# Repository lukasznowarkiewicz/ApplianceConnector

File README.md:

# Appliance connector

## Initial idea - visible gap on the market

The history behing this device came from my experience - I used to install smart home systems and saw some market gap in integrating smart home devices which oryginally was not intended to be "smart". I have in mind devices controlled over infrared, like air condationers, TVs, home theaters, audio systems, satellite and cable boxes, projectors, controlled over serial port (RS-232), like projectors, some audio entertainment systems, video conferencing systems, surveillance camera systems, etc., finishing on most simple, controlled with dry contact, like garage and gate openers, access control systems or blinds and curtains systesm, to just name a few. Backbone of most smart home systems in the end, almost always is TCP/IP network. Proabably the most universal method between both vendor locked and open smart home systems is communication via REST API. This device main prupose was to cover this gap, allow integration of all listed devices in thoughtfully manner. 

## Similar devices

Back in 2019, when we were working on this device, already some alternatives existed. There were deivces, which adresses only part of the problem. To list a few:

### Global Cache iTach

- **Pros**: Supports various connection options, compact, compatible with many systems.
- **Cons**: Setup complexity, may not suit simple needs, separate devices for RS232 and IR, high price

### BroadLink RM Pro+

- **Pros**: Affordable, supports IR and RF 433MHz, works with major voice assistants.
- **Cons**: RF control issues reported, app usability, lack of REST API.

### Remotec AC Master ZXT-600

- **Pros**: Specialized for AC control, supports major brands, energy-efficient.
- **Cons**: Limited to AC, setup complexity with certain hubs, lack of REST API.

### Blastbot IR Blaster

- **Pros**: Smartphone and voice control, supports schedules.
- **Cons**: Cloud dependency, IR only, lack of REST API.

### Remotec ZXT-310US

- **Pros**: Z-Wave to IR for AV devices, supports learning IR codes.
- **Cons**: Focus on AV, manual configuration for uncommon devices, lack of REST API.

### Hank IR Transceiver

- **Pros**: Z-Wave Plus, IR learning, compact.
- **Cons**: AV control focus, setup technicality, lack of REST API.

### Xiaomi Universal IR Remote Controller

- **Pros**: Very affordable, wide device support, integrates with Mi Home.
- **Cons**: Wi-Fi dependency, app/setup challenges for non-Chinese speakers, lack of REST API.

### Logitech Harmony

- **Pros**: Broad device compatibility, advanced automation, supports multiple connection types.
- **Cons**: Higher cost, discontinued models may affect support, lack of REST API.

## First prototype

First prototype was rough. Designed in `Autodesk Eagle` (shortly after buying it from CadSoft). It only purpose was to get rid off breadboards, which often cause more problems than circuit itself. This devkit was an extension to `Lolin32 Lite` prototyping board. This board I would call as "it ain't much, but it honest work" and most important allowed us quick start working on the software.

It has necessary components for testing initially agreed functionalities:
- IR leds for controlling devices
- IR receiver `PNA460XM`
- two experimental touch buttons (ESP32 has itself option for capacitive buttons support, but in the end we were unable to figure out how to make it work)
- connector for `TTTP223` based touch button module
- `WS2812B` Leds for showing status of the device

## Functional requirements and UI design

At this point we more or less know how device should function, which features implement. Form of the device was not clear yet, but anyway it didn't stop us from working on software. Basic user interface was designed in `Affinity Designer`. Simple mockup of the software, not functional, but give us good base for creating user interface in web technologies.

## Software Development

The web server runs directly on the ESP32, necessitating that the webpage be as simple and lightweight as possible. With only 4MB of storage available, every kilobyte counted. Most images used were .svg, and wherever feasible, they were generated using CSS to save space.

The ESP32 operates on `ESP-IDF FreeRTOS`. Developing such an advanced application in plain C—especially incorporating functions like Wi-Fi connection, filesystem management, and web server functionalities—would significantly increase the app's complexity.

### Frontend

Given the storage limitations, the frontend was designed to be straightforward and lightweight. This is why we opted not to use any frameworks for creating the GUI. It was crafted using simple HTML, with CSS for styling and JavaScript for websockets to minimize overhead and ensure efficiency.

https://github.com/lukasznowarkiewicz/ApplianceConnector/assets/82212257/3271daf3-c359-4126-b65f-c0a6bbfbe71e

### Backend

The backend of this application on the ESP32, utilizing ESP-IDF FreeRTOS, comprises various components, each managed by specific files:

- **Webserver**: `webserver.c` and `webserver.h` handle HTTP requests, serving the GUI files and processing API calls from the frontend. `webserver_types.h` likely defines the structures and enums used by the webserver.

- **Wi-Fi Connection**: `netConf.c` and `netConf.h` are responsible for configuring the Wi-Fi connection, handling tasks such as connecting to the Wi-Fi network and managing network settings.

- **Infrared Control**:
  - Sending IR commands: `irsend.c` and `irsend.h` manage the sending of IR commands to devices.
  - Receiving IR commands: `irrecv.c` and `irrecv.h` handle the reception of IR signals from remote controls.

- **UART Communication**: `tcpserial.c` and `tcpserial.h` handle of UART communication.

- **LED Control**: `led.c` and `led.h` are used for controlling LED indicators on the ESP32, such as showing the status of the device or Wi-Fi connection.

- **Relay Control**: `relay.c` and `relay.h` manage the activation and deactivation of relays for controlling dry contacts.

- **Button Input**: `button.c` and `button.h` handle input from physical buttons on the ESP32 device, allowing for user interaction without the web interface.

### Testing infrared

Testing receiving commands from IR:

https://github.com/lukasznowarkiewicz/ApplianceConnector/assets/82212257/00d33be0-9f63-4c23-b90f-50ff3d0fc727

Testing sending commands over IR:

https://github.com/lukasznowarkiewicz/ApplianceConnector/assets/82212257/5f554944-b339-42f7-858e-584611f51841

Saving received commands to text file (as a config):

https://github.com/lukasznowarkiewicz/ApplianceConnector/assets/82212257/204f5668-1959-4dcd-b433-fa26de5b123a

### Testing UART

https://github.com/lukasznowarkiewicz/ApplianceConnector/assets/82212257/dbb3c007-76f6-457e-a3c8-33a27682dad4

### Testing relays

https://github.com/lukasznowarkiewicz/ApplianceConnector/assets/82212257/7d674879-574c-41a6-804a-36f65532bcf2

## Enclosure

After we made first functioning prorotype - it was time to pack this device into sleek housing. Many ideas was both designed and 3d printed. 

Casing was designed in Fusion360:

REV 5 is the last casing we stick to and designed custom board for it. It has touch button on the top, translucent casing allowing both IR and visible light from RGB LEDs to go through, place at the bottom for slide-in mounting brackets (allowing for mounting it on the ceiling, to ziptie to something, etc.)

## Hardware

Electronic part of the design consists mainly on two boards:
- upper one with ESP32 module, IR LEDs and IR receiver
- lower one with terminal blocks for screwing wires of the RS232 device, dry contact controlled deivces, supply power via terminal block, side or bottom micro-USB cable and headphone jacks for connecting remote IR transmitters. Hole in the middle allow guiding wires through and then wrap them around the deivce.

In the folder `hardwareElectronics` `Eagle` project can be found. Unfortunately the most recent version has been lost and I've simply attached the last backup I could find.

## Project abandon

Due to start of the studies and lack of free time, this project died spontaneously. Now when I'm pushing those assets and writing this readme (about the time of finishing my masters degree) I look at it with a wink. Today with ease I've found a few of the market devices doing exactly that. Even cool project ESPHome does exactly that. But overall at the time it was great experiece.

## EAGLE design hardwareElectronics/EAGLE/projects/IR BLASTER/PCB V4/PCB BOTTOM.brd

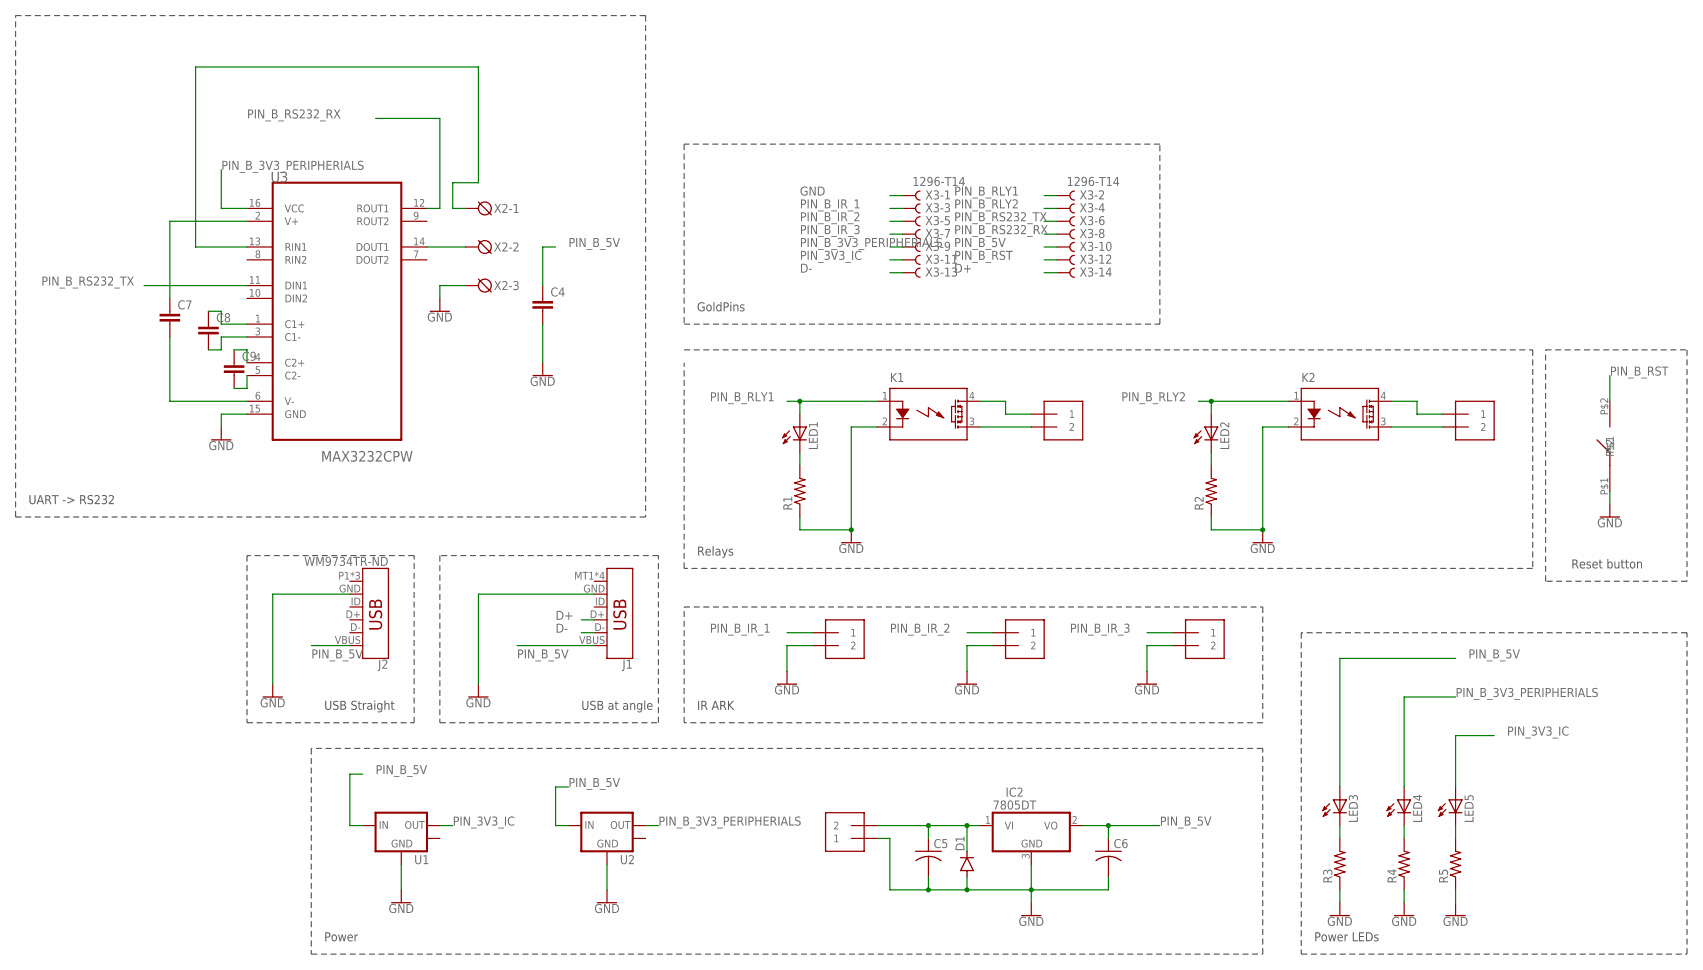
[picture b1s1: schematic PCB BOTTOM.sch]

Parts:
C4, C7, C8, C9: C-EUC0805K; C0805K
C5, C6: C-USC1206K; C1206K
D1: DIODE-SOD80C; SOD80C
IC2: 7805DT; TO252
IR1, IR2, IR3: 1X2-3.5MM
J1: USB_MICRO-B_SMT; USB-MICROB
J2: WM9734TR-ND; USB-B-MICRO-SMD_VERT
K1, K2: CPC1008N; SOIC-4-2.54
LED1, LED2, LED3, LED4, LED5: LEDCHIP-LED0805; CHIP-LED0805
PWR: 1X2-3.5MM
R1, R2, R3, R4, R5: R-US_M0805; M0805
RLY1, RLY2: 1X2-3.5MM
U1, U2: LM1117-1.8; SOT223
U3: MAX3232CPW; SOP65P640X120-16N
U$1: MICRO_SWITCH_AT_ANGLE
X2: DG3XX-03-3.5; DG350-3.5-03P
X3: 1296-T14; 1296-14

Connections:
D+: J1.D+, X3.14
D-: J1.D-, X3.13
GND: C4.2, C5.2, C6.2, D1.A, IC2.3 (GND), IR1.2, IR2.2, IR3.2, J1.GND, J2.GND, K1.2 (K), K2.2 (K), PWR.1, R1.1, R2.1, R3.1, R4.1, R5.1, U1.1 (GND), U2.1 (GND), U3.15 (GND), U$1.P$1, X2.3, X3.1
unnamed: K1.3 (D2), RLY1.2
unnamed: K1.4 (D1), RLY1.1
unnamed: LED1.C, R1.2
unnamed: K2.3 (D2), RLY2.2
unnamed: K2.4 (D1), RLY2.1
unnamed: LED2.C, R2.2
unnamed: U3.14 (DOUT1), X2.2
unnamed: U3.13 (RIN1), X2.1
unnamed: LED3.C, R3.2
unnamed: LED4.C, R4.2
unnamed: LED5.C, R5.2
unnamed: C7.1, U3.2 (V+)
unnamed: C7.2, U3.6 (V-)
unnamed: C9.1, U3.4 (C2+)
unnamed: C9.2, U3.5 (C2-)
unnamed: C8.2, U3.3 (C1-)
unnamed: C5.1, D1.C, IC2.1 (VI), PWR.2
unnamed: C8.1, U3.1 (C1+)
PIN_3V3_IC: LED5.A, U1.2 (OUT), X3.11
PIN_B_3V3_PERIPHERIALS: LED4.A, U2.2 (OUT), U3.16 (VCC), X3.9
PIN_B_5V: C4.1, C6.1, IC2.2 (VO), J1.VBUS, J2.VBUS, LED3.A, U1.3 (IN), U2.3 (IN), X3.10
PIN_B_IR_1: IR1.1, X3.3
PIN_B_IR_2: IR2.1, X3.5
PIN_B_IR_3: IR3.1, X3.7
PIN_B_RLY1: K1.1 (A), LED1.A, X3.2
PIN_B_RLY2: K2.1 (A), LED2.A, X3.4
PIN_B_RS232_RX: U3.12 (ROUT1), X3.8
PIN_B_RS232_TX: U3.11 (DIN1), X3.6
PIN_B_RST: U$1.P$2, X3.12

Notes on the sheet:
USB Straight
USB at angle
Power
IR ARK
Power LEDs
Reset button
Relays
GoldPins
UART -> RS232

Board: 2 copper layers, 34 parts (3 on the bottom side), 32 nets, no tracks yet.

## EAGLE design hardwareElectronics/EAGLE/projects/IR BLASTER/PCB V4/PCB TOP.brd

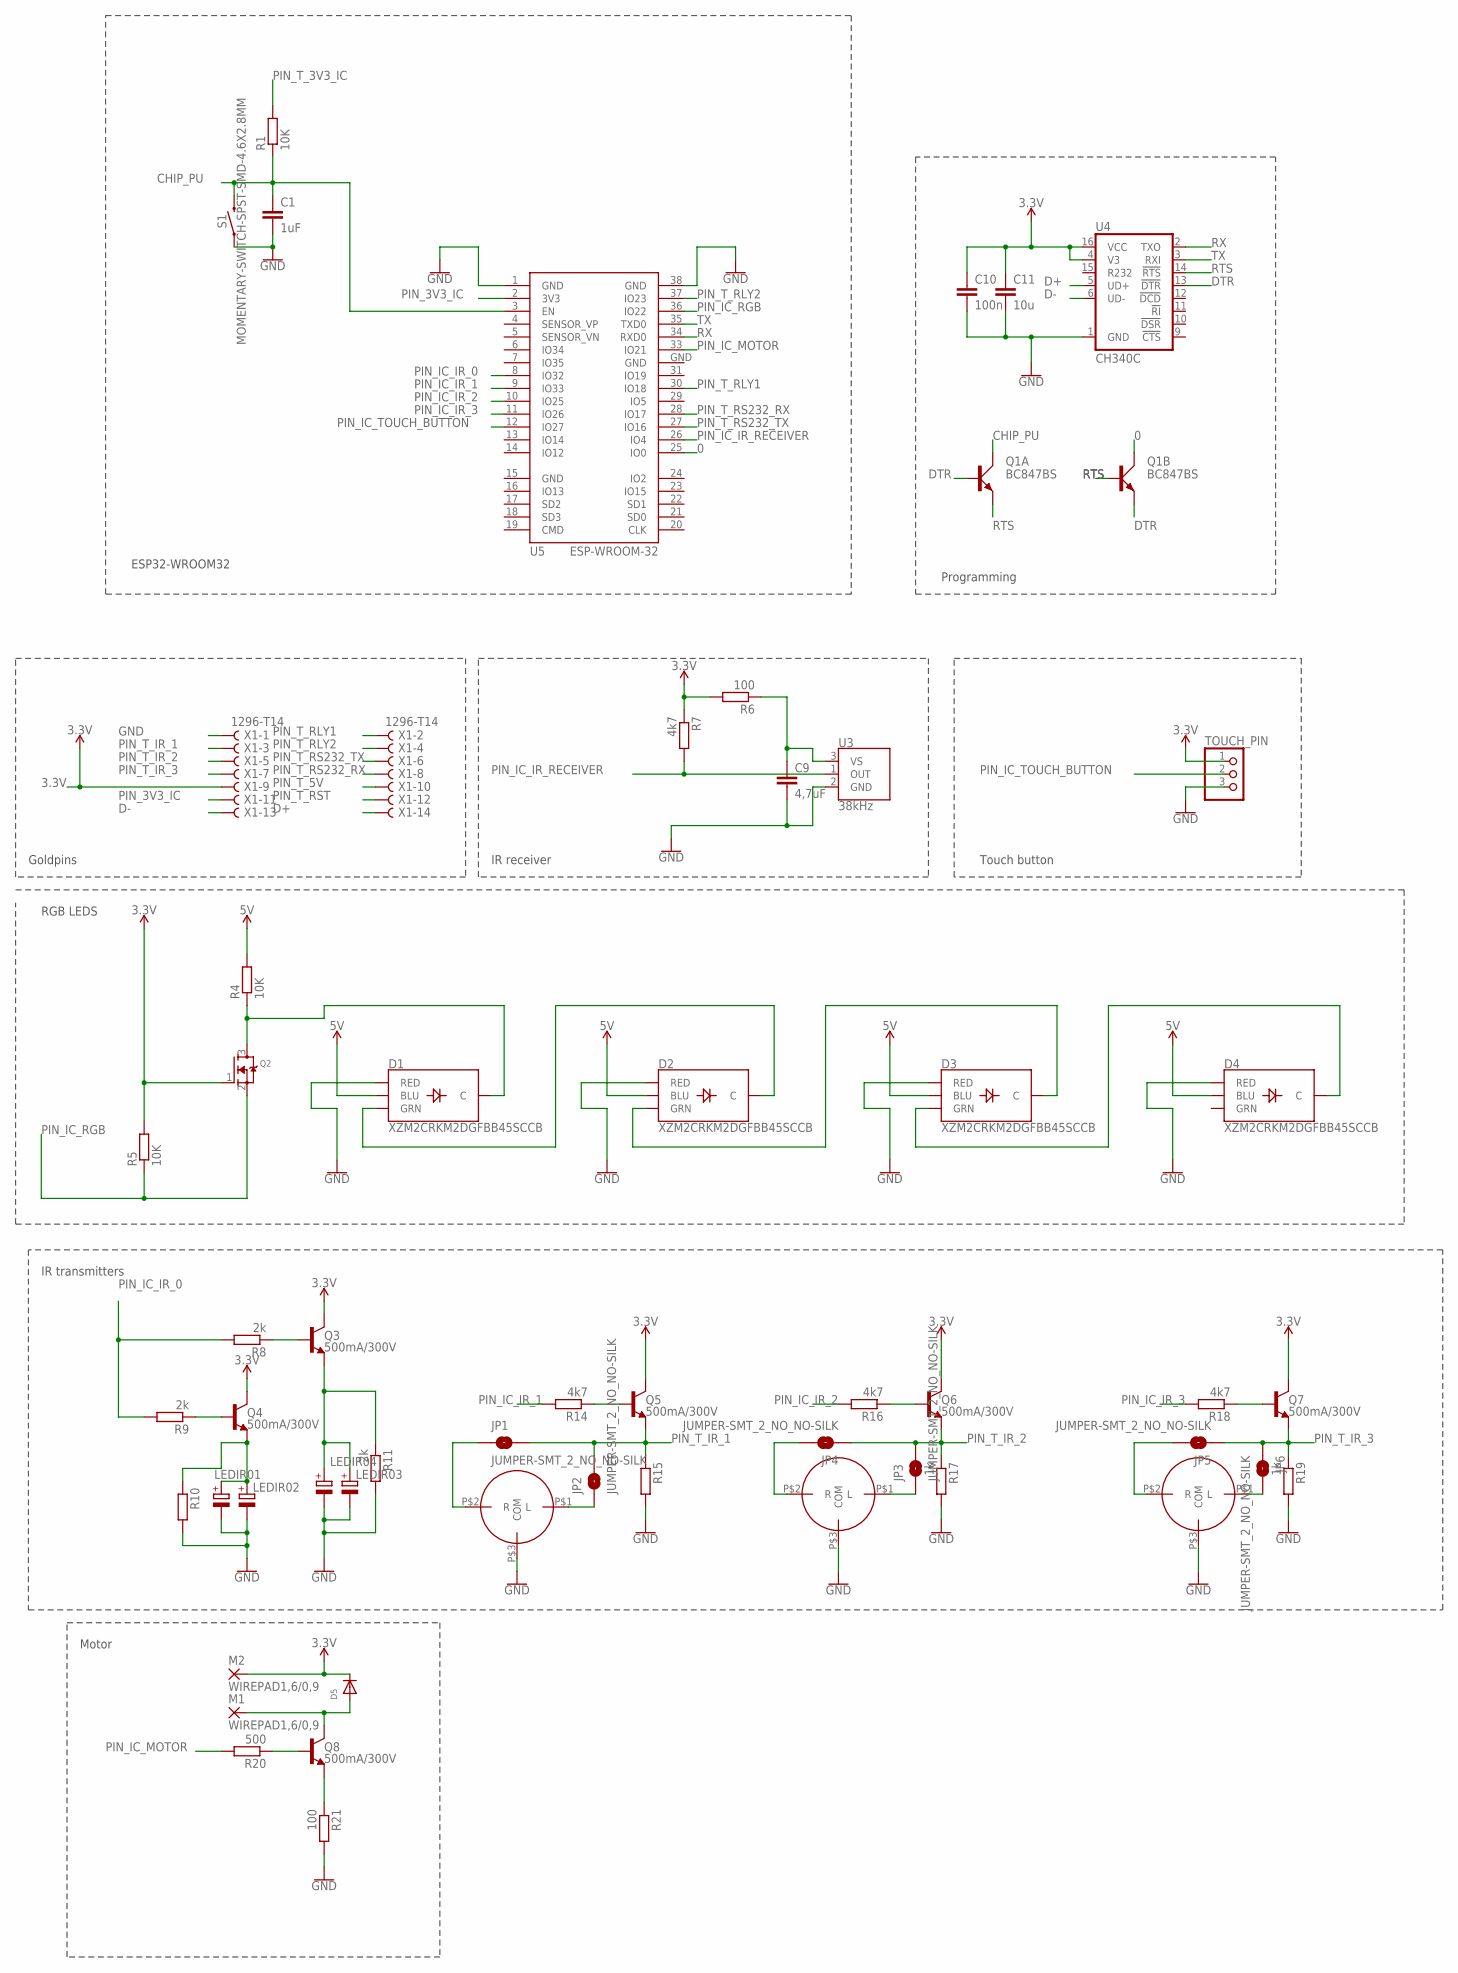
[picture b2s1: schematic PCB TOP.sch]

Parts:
C1: 1uF; C0603K
C9: 4,7uF; C0603K
C10: 100n; C0603K
C11: 10u; C0603K
D1, D2, D3, D4: XZM2CRKM2DGFBB45SCCB; PLCC4SMDLED
D5: DIODESOD-323F; SOD-323F
JP1, JP2, JP3, JP4, JP5, JP6: JUMPER-SMT_2_NO_NO-SILK; SMT-JUMPER_2_NO_NO-SILK
LEDIR01, LEDIR02, LEDIR03, LEDIR04: CPOL-EUB/3528-21R; B/3528-21R
M1, M2: WIREPAD1,6/0,9; 1,6/0,9
Q1: BC847BS; SOT363_PHILIPS
Q2: MOSFET-NREFLOW; SOT23
Q3, Q4, Q5, Q6, Q7, Q8: 500mA/300V; SOT23-3
R1, R4, R5: 10K; R0603
R6, R21: 100; R0603
R7, R14, R16, R18: 4k7; R0603
R8, R9, R10, R11: 2k; R0603
R15, R17, R19: 1k; R0603
R20: 500; R0603
S1: MOMENTARY-SWITCH-SPST-SMD-4.6X2.8MM; TACTILE_SWITCH_SMD_4.6X2.8MM
TOUCH_PIN: PINHD-1X3; 1X03
U3: 38kHz; TSOP382
U4: CH340C; SO016
U5: ESP-WROOM-32
U$1, U$2, U$3: JACK3.5MM
X1: 1296-T14; 1296-14

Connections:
0: Q1.3 (C), U5.25 (IO0)
3.3V: C10.1, C11.1, D5.C, M2.1, Q2.1 (G), Q3.3 (C), Q4.3 (C), Q5.3 (C), Q6.3 (C), Q7.3 (C), R5.2, R6.2, R7.1, TOUCH_PIN.1, U4.4 (V3), U4.16 (VCC), X1.9
5V: D1.3 (BLU), D2.3 (BLU), D3.3 (BLU), D4.3 (BLU), R4.2
CHIP_PU: C1.1, Q1.6 (C), R1.1, S1.3 (2), S1.4 (2), U5.3 (EN)
D+: U4.5 (UD+), X1.14
D-: U4.6 (UD-), X1.13
DTR: Q1.2 (B), Q1.4 (E), U4.13 (!DTR)
GND: C1.2, C9.2, C10.2, C11.2, D1.1 (RED), D2.1 (RED), D3.1 (RED), D4.1 (RED), LEDIR01.-, LEDIR02.-, LEDIR03.-, LEDIR04.-, R10.2, R11.2, R15.2, R17.2, R19.2, R21.2, S1.1, S1.2 (1), TOUCH_PIN.3, U3.2 (GND), U4.1 (GND), U5.1 (GND), U5.15 (GND), U5.38 (GND), U5.GND, U$1.P$3 (COM), U$2.P$3 (COM), U$3.P$3 (COM), X1.1
unnamed: JP6.2, U$3.P$1 (L)
unnamed: JP2.1, U$1.P$1 (L)
unnamed: JP1.1, U$1.P$2 (R)
unnamed: JP4.2, U$2.P$2 (R)
unnamed: JP3.1, U$2.P$1 (L)
unnamed: D1.4 (C), Q2.3 (D), R4.1
unnamed: JP5.2, U$3.P$2 (R)
unnamed: D1.2 (GRN), D2.4 (C)
unnamed: C9.1, R6.1, U3.3 (VS)
unnamed: D2.2 (GRN), D3.4 (C)
unnamed: LEDIR01.+, LEDIR02.+, Q4.2 (E), R10.1
unnamed: D3.2 (GRN), D4.4 (C)
unnamed: LEDIR03.+, LEDIR04.+, Q3.2 (E), R11.1
unnamed: Q3.1 (B), R8.1
unnamed: Q4.1 (B), R9.1
unnamed: Q5.1 (B), R14.1
unnamed: Q6.1 (B), R16.1
unnamed: Q7.1 (B), R18.1
unnamed: Q8.1 (B), R20.1
unnamed: D5.A, M1.1, Q8.3 (C)
unnamed: Q8.2 (E), R21.1
PIN_3V3_IC: U5.2 (3V3), X1.11
PIN_IC_IR_0: R8.2, R9.2, U5.8 (IO32)
PIN_IC_IR_1: R14.2, U5.9 (IO33)
PIN_IC_IR_2: R16.2, U5.10 (IO25)
PIN_IC_IR_3: R18.2, U5.11 (IO26)
PIN_IC_IR_RECEIVER: R7.2, U3.1 (OUT), U5.26 (IO4)
PIN_IC_MOTOR: R20.2, U5.33 (IO21)
PIN_IC_RGB: Q2.2 (S), R5.1, U5.36 (IO22)
PIN_IC_TOUCH_BUTTON: TOUCH_PIN.2, U5.12 (IO27)
PIN_T_3V3_IC: R1.2
PIN_T_5V: X1.10
PIN_T_IR_1: JP1.2, JP2.2, Q5.2 (E), R15.1, X1.3
PIN_T_IR_2: JP3.2, JP4.1, Q6.2 (E), R17.1, X1.5
PIN_T_IR_3: JP5.1, JP6.1, Q7.2 (E), R19.1, X1.7
PIN_T_RLY1: U5.30 (IO18), X1.2
PIN_T_RLY2: U5.37 (IO23), X1.4
PIN_T_RS232_RX: U5.28 (IO17), X1.8
PIN_T_RS232_TX: U5.27 (IO16), X1.6
PIN_T_RST: X1.12
RTS: Q1.1 (E), Q1.5 (B), U4.14 (!RTS)
RX: U4.2 (TXO), U5.34 (RXD0)
TX: U4.3 (RXI), U5.35 (TXD0)

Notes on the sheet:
ESP32-WROOM32
Programming
Goldpins
IR receiver
Touch button
RGB LEDS
IR transmitters
Motor

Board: 2 copper layers, 55 parts (1 on the bottom side), 48 nets, no tracks yet.

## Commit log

2024-03-25 Added hardware part
2024-03-25 Added images and videos
2024-03-25 Added UI design folder
2024-03-25 Added software
2024-03-25 Added enclosure
2024-03-25 Added screenshot
2024-03-25 Added structure to readme
2024-03-25 Update README.md - Initial idea
2024-03-25 Update README.md - Similar devices
2024-03-25 Update README.md - added render
2024-03-25 Update README.md - First prototype
2024-03-25 Update README.md - UI design
2024-03-25 Update README.md - Software Development
2024-03-25 Update README.md - added videos
2024-03-25 Update README.md - added renders of the enclosure
2024-03-26 Update README.md - the ending

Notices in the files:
parts and their libraries:
SparkFun-Connectors: Licensing: Creative Commons ShareAlike 4.0 International - https://creativecommons.org/licenses/by-sa/4.0
vreg-linear: 2009 Draw by Ivan A-R. License CC-BY-SA 3.0
esp32: Creative Commons Attribution-ShareAlike 4.0 International
